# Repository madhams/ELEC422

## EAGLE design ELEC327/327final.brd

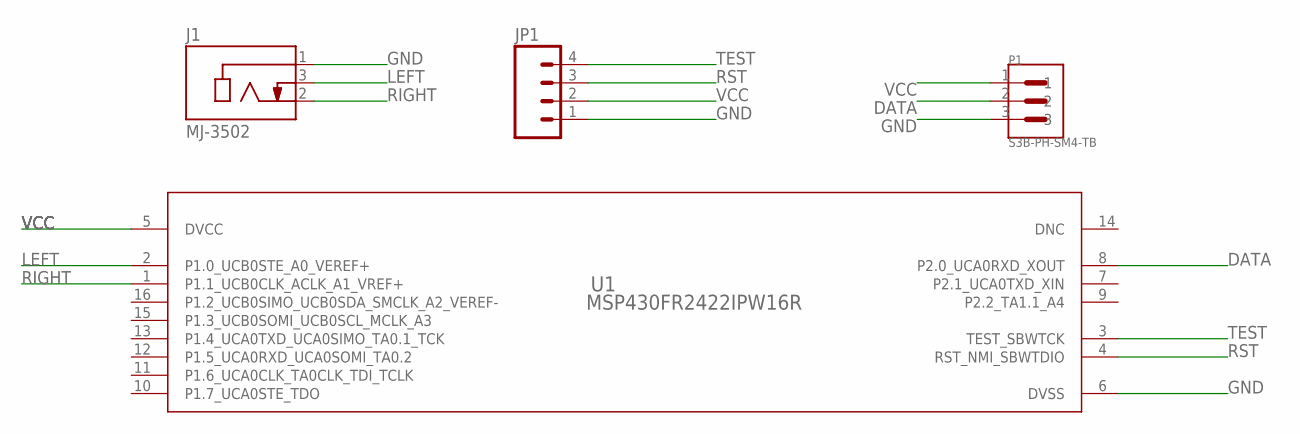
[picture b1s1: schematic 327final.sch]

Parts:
J1: MJ-3502; CUI_MJ-3502
JP1: HEADER_1X04LOCK; 1X04_LOCK
P1: S3B-PH-SM4-TB; JST_S3B-PH-SM4-TB
U1: MSP430FR2422IPW16R; PW0016A_N

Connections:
DATA: P1.2, U1.8 (P2.0_UCA0RXD_XOUT)
DNC: U1.14 (DNC)
GND: J1.1, JP1.1, P1.3, U1.6 (DVSS)
LEFT: J1.3, U1.2 (P1.0_UCB0STE_A0_VEREF+)
RIGHT: J1.2, U1.1 (P1.1_UCB0CLK_ACLK_A1_VREF+)
RST: JP1.3, U1.4 (RST_NMI_SBWTDIO)
TEST: JP1.4, U1.3 (TEST_SBWTCK)
VCC: JP1.2, P1.1, U1.5 (DVCC)

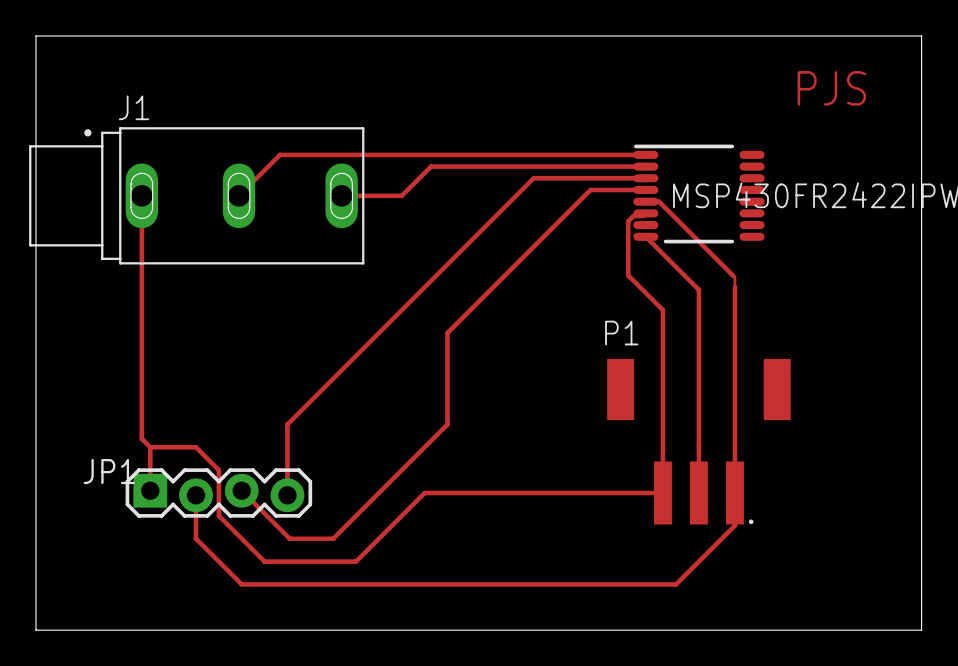
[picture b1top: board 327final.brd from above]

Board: 2 copper layers, 49.2 x 33.0 mm, 4 parts (0 on the bottom side), 7 nets.

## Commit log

2023-02-28 Add files via upload
    S box module for decoder
2023-04-09 removed rc
2023-04-09 synth
2023-04-12 changed rc
2023-05-01 added padframe
2023-05-01 Added "Rice" test files

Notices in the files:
parts and their libraries:
COPYRIGHT: Copyright (C) 2023 Ultra Librarian. All rights reserved.
